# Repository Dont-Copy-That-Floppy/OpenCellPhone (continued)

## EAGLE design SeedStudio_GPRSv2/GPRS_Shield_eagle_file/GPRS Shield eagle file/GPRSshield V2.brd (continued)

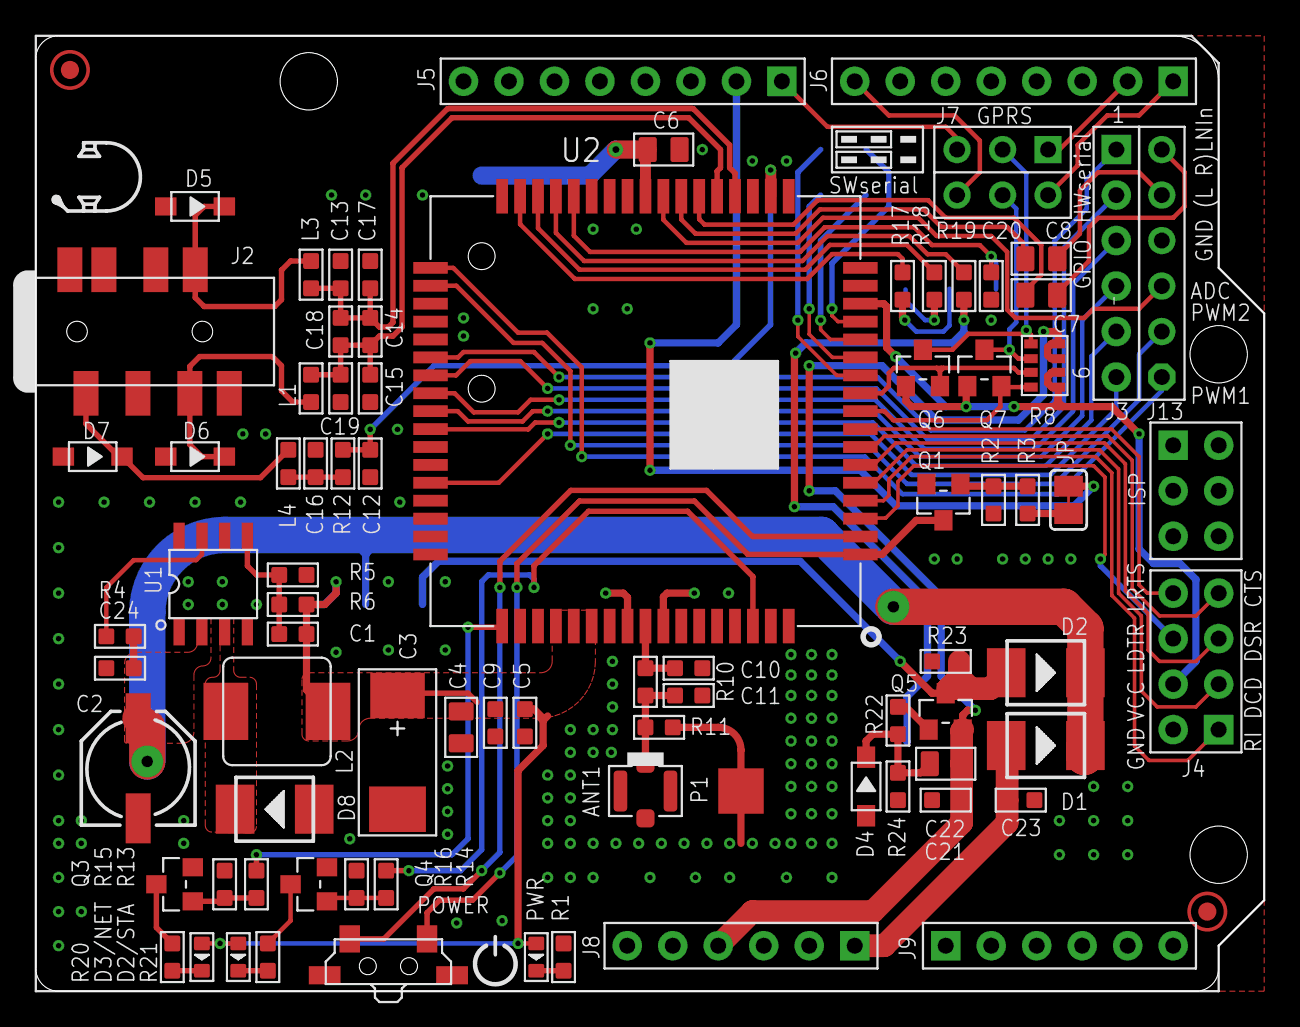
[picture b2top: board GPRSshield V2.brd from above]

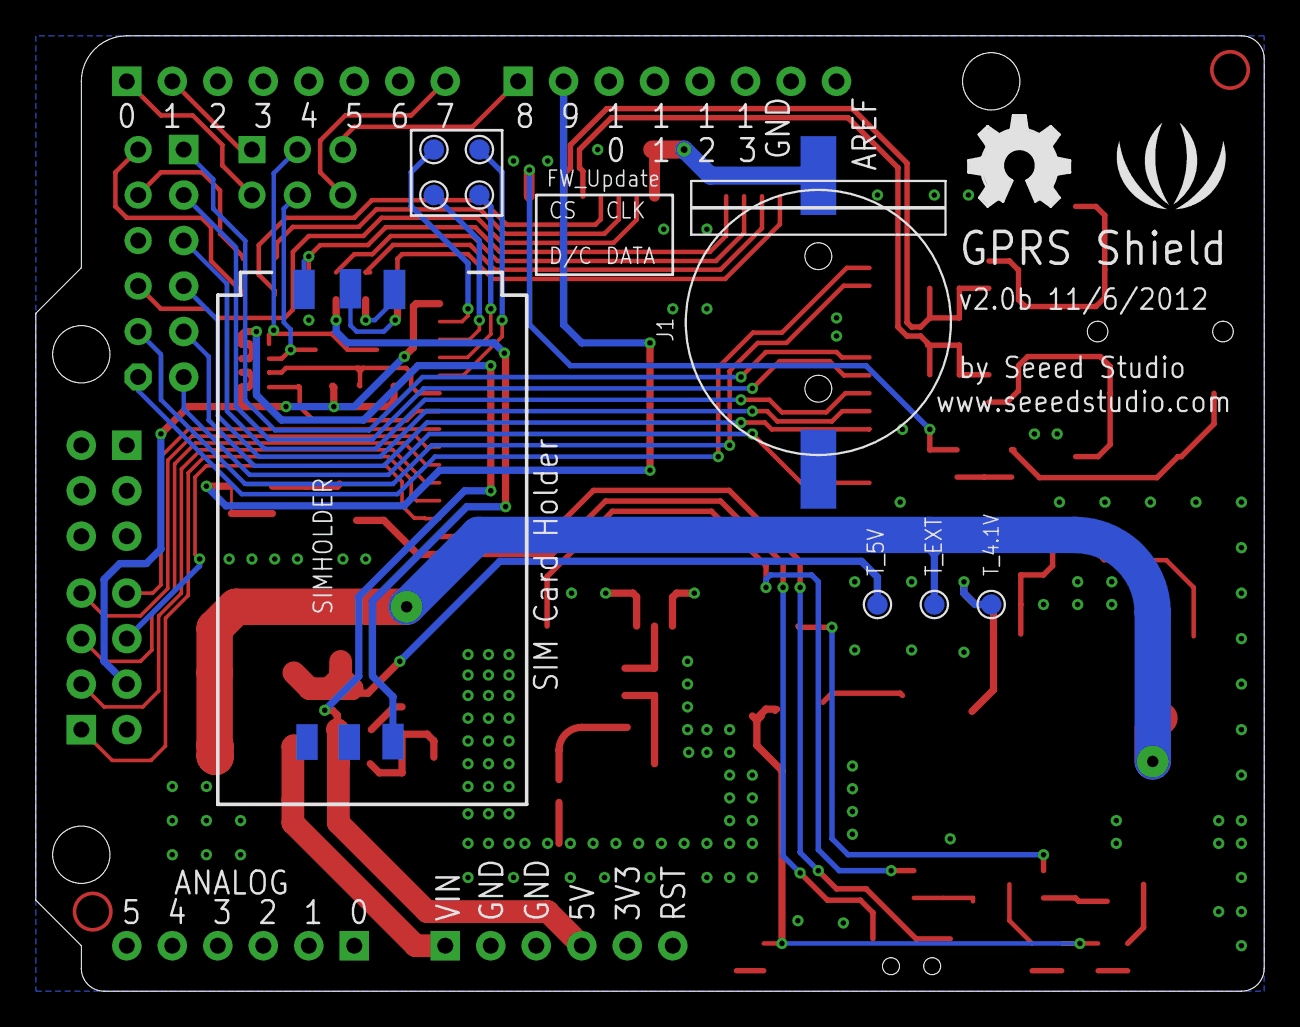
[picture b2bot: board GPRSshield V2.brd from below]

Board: 2 copper layers, 68.6 x 53.3 mm, 91 parts (11 on the bottom side), 74 nets.

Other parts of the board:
U$26: LOGO_SILK
U$28: OSHW_FILLX200_NOTEXT

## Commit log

2014-08-17 08162014
2014-08-18 PrototypePhone
    08/18/2014, not quite finished
2014-08-20 8/19
    using Due, RA8875, 4.3" TFT, new libs
2014-08-23 library/sketch/reference addition,
2014-08-25 number pad sensing and Due references
2014-10-19 Working Phone
    Calling, Answering, Hanging up, Displaying numbers, receiving input
2014-10-19 ASCII table
2014-11-05 Whole bunch of new features
2014-11-05 Answer Screen Bug fix
2014-11-05 caller ID, bug fixes
2014-11-05 bug fixes
2014-11-05 caller id bug fix
2014-11-07 11-7-2014,3:48pm
2014-11-07 don't need backup
2014-11-07 Readme fixed
2014-11-12 Only SMS missing
2014-11-18 Library fixs
2014-11-20 Text Rotate bug fix
2014-11-20 additional bug fixes RA8875.cpp
2014-11-20 Additional bug fixes RA8875.cpp and new IDE
2014-11-21 tidy up, SMS screen additions
2014-12-07 Notification Area
2014-12-07 orrection delayForUart logical error
2014-12-07 Button Lock bug fix
2014-12-07 Touch Bug
2014-12-07 AM time bug fix
2014-12-08 AM_PM bug fix
2016-01-08 Multiple Bug Fixes, Code speed-ups, feature adds
    Simplified code tx and ty values, as well as position values
    Simplified the time placement values
    Added time display to passcode screen and reformated the display of time
    1/5/2016
    Added transitor based power control of SIM module
    Removed psuedo-boot sequence
2016-01-18 Bug fix 1-18-2016
    Removed or commented out unused variables, corrected code, created new
    folder for easy "install" and usage of code on arduino
2016-01-18 Renamed files
2016-04-03 Screen Feature and Debouncing Test
    Added function to try to eliminate debouncing at fast interchange rates.
    Screen Darkens just before sleep
2016-07-14 Major Bug Fixes and Improvements
    Libraries Updated
    Call Ended Fixed
    Fixed Debouncing Issue and improved touch algorithum
    Added Display for Battery Level
    Removed repeative code
    Text Screen and text message functions bug fixes
2016-07-14 Wrong INO File Upload
2016-08-15 Time and variable Optimization
2016-08-15 Time and variable Optimization_
2016-11-02 Bug Fixes && Code Improvements
2018-08-13 Directory Merge
2018-08-13 remove
2025-02-23 -- update
2025-04-12 - major overhaul
2025-04-12 - major cleanup
2025-04-12 - readme corrections
